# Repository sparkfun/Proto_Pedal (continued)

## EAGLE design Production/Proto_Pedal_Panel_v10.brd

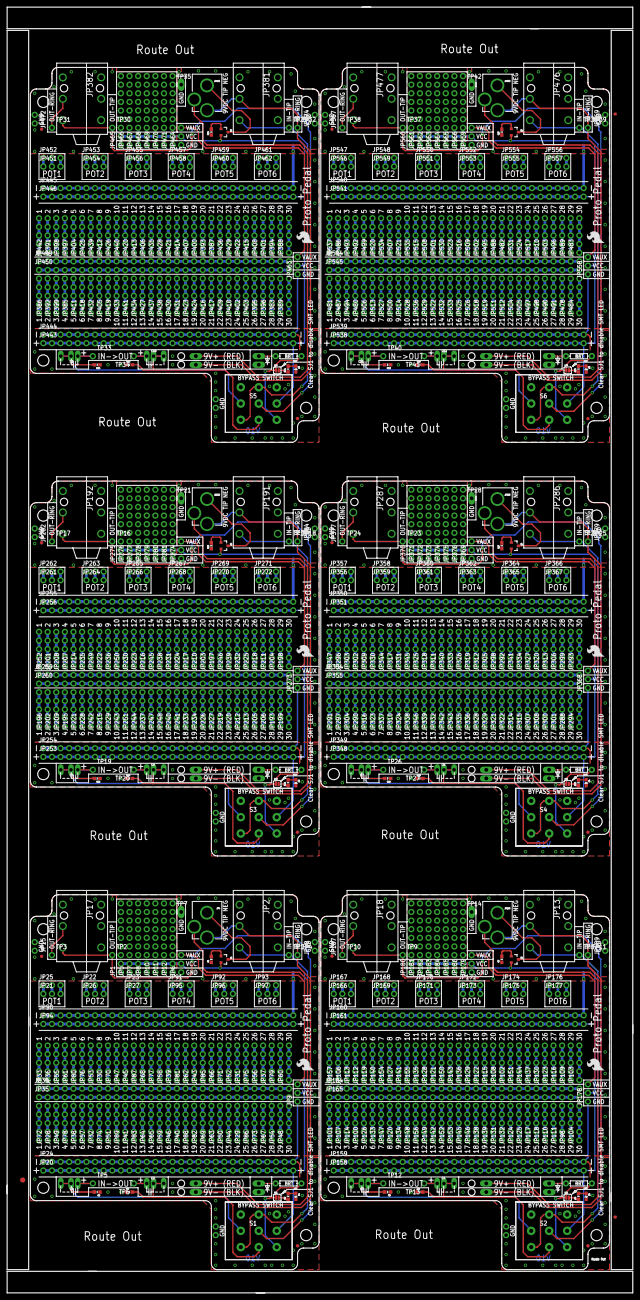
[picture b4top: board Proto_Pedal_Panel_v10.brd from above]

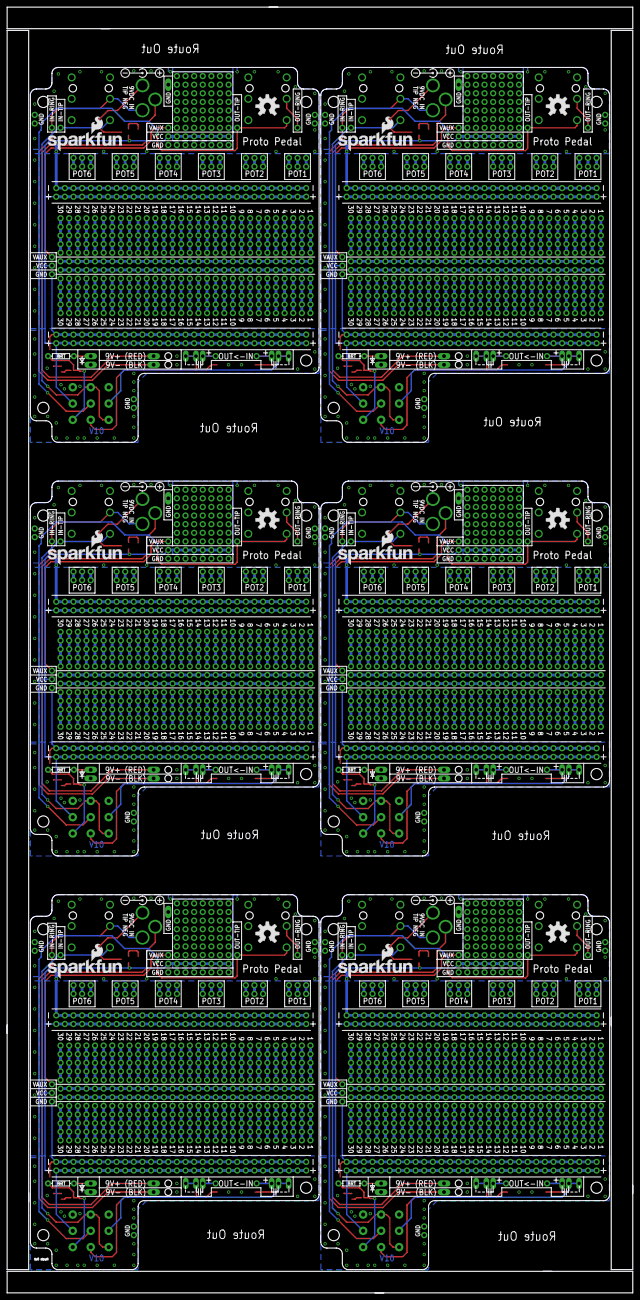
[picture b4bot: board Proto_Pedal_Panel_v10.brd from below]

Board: 2 copper layers, 184.4 x 379.0 mm, 735 parts (12 on the bottom side), 588 nets.

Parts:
C1, C3, C5, C7, C9, C11: C in; DUAL-CAP
C2, C4, C6, C8, C10, C12: C out; DUAL-CAP
D1, D2, D3, D4, D5, D6: RED; LED-0603
E$1: FIDUCIAL-1.5X3
E$5, E$6: FIDUCIAL-1X2
FID1, FID2, FID3, FID4, FID5, FID6, FID7, FID8, FID9, FID10, FID11, FID12: FIDUCIAL1X2; FIDUCIAL-1X2
JP1, JP5, JP7, JP8, JP10, JP11, JP12, JP180, JP181, JP182, JP183, JP184, JP185, JP186, JP275, JP276, JP277, JP278, JP279, JP280, JP281, JP370, JP371, JP372, JP373, JP374, JP375, JP376, JP465, JP466, JP467, JP468, JP469, JP470, JP471, JP560, JP561, JP562, JP563, JP564, JP565, JP566: 1x9; 1X09_NO_SILK
JP2, JP13, JP191, JP286, JP381, JP476: INPUT JACK; AUDIO-JACK-.25-INCH-HORIZ-PTH
JP3, JP163, JP258, JP353, JP448, JP543: 9VBattery; 1X02_LONGPADS
JP4, JP190, JP285, JP380, JP475, JP570: POWER_JACK_TIP_NEGATIVE; POWER-BARRELJACK-PTH-LOCK-FIXED
JP6, JP9, JP21, JP22, JP23, JP25, JP26, JP27, JP91, JP92, JP93, JP95, JP96, JP97, JP166, JP167, JP168, JP169, JP170, JP171, JP172, JP173, JP174, JP175, JP176, JP177, JP178, JP179, JP261, JP262, JP263, JP264, JP265, JP266, JP267, JP268, JP269, JP270, JP271, JP272, JP273, JP274, JP356, JP357, JP358, JP359, JP360, JP361, JP362, JP363, JP364, JP365, JP366, JP367, JP368, JP369, JP451, JP452, JP453, JP454, JP455, JP456, JP457, JP458, JP459, JP460, JP461, JP462, JP463, JP464, JP546, JP547, JP548, JP549, JP550, JP551, JP552, JP553, JP554, JP555, JP556, JP557, JP558, JP559: 1x3; 1X03_NO_SILK
JP14, JP162, JP257, JP352, JP447, JP542: PTH-LED; 1X02_LONGPADS
JP15, JP16, JP19, JP187, JP188, JP189, JP282, JP283, JP284, JP377, JP378, JP379, JP472, JP473, JP474, JP567, JP568, JP569: 1x2; 1X02_NO_SILK
JP17, JP18, JP192, JP287, JP382, JP477: OUTPUT JACK; AUDIO-JACK-.25-INCH-HORIZ-PTH
JP20, JP24, JP34, JP35, JP90, JP94, JP158, JP159, JP160, JP161, JP164, JP165, JP253, JP254, JP255, JP256, JP259, JP260, JP348, JP349, JP350, JP351, JP354, JP355, JP443, JP444, JP445, JP446, JP449, JP450, JP538, JP539, JP540, JP541, JP544, JP545: 1x30; 1X30_NO_SILK
JP28, JP29, JP30, JP31, JP32, JP33, JP36, JP37, JP38, JP39, JP40, JP41, JP42, JP43, JP44, JP45, JP46, JP47, JP48, JP49, JP50, JP51, JP52, JP53, JP54, JP55, JP56, JP57, JP58, JP59, JP60, JP61, JP62, JP63, JP64, JP65, JP66, JP67, JP68, JP69, JP70, JP71, JP72, JP73, JP74, JP75, JP76, JP77, JP78, JP79, JP80, JP81, JP82, JP83, JP84, JP85, JP86, JP87, JP88, JP98, JP99, JP100, JP101, JP102, JP103, JP104, JP105, JP106, JP107, JP108, JP109, JP110, JP111, JP112, JP113, JP114, JP115, JP116, JP117, JP118, JP119, JP120, JP121, JP122, JP123, JP124, JP125, JP126, JP127, JP128, JP129, JP130, JP131, JP132, JP133, JP134, JP135, JP136, JP137, JP138, JP139, JP140, JP141, JP142, JP143, JP144, JP145, JP146, JP147, JP149, JP150, JP151, JP152, JP153, JP154, JP155, JP156, JP157, JP193, JP194, JP195, JP196, JP197, JP198, JP199, JP200, JP201, JP202, JP203, JP204, JP205, JP206, JP207, JP208, JP209, JP210, JP211, JP212, JP213, JP214, JP215, JP216, JP217, JP218, JP219, JP220, JP221, JP222, JP223, JP224, JP225, JP226, JP227, JP228, JP229, JP230, JP231, JP232, JP233, JP234, JP235, JP236, JP237, JP238, JP239, JP240, JP241, JP242, JP244, JP245, JP246, JP247, JP248, JP249, JP250, JP251, JP252, JP288, JP289, JP290, JP291, JP292, JP293, JP294, JP295, JP296, JP297, JP298, JP299, JP300, JP301, JP302, JP303, JP304, JP305, JP306, JP307, JP308, JP309, JP310, JP311, JP312, JP313, JP314, JP315, JP316, JP317, JP318, JP319, JP320, JP321, JP322, JP323, JP324, JP325, JP326, JP327, JP328, JP329, JP330, JP331, JP332, JP333, JP334, JP335, JP336, JP337, JP339, JP340, JP341, JP342, JP343, JP344, JP345, JP346, JP347, JP383, JP384, JP385, JP386, JP387, JP388, JP389, JP390, JP391, JP392, JP393, JP394, JP395, JP396, JP397, JP398, JP399, JP400, JP401, JP402, JP403, JP404, JP405, JP406, JP407, JP408, JP409, JP410, JP411, JP412, JP413, JP414, JP415, JP416, JP417, JP418, JP419, JP420, JP421, JP422, JP423, JP424, JP425, JP426, JP427, JP428, JP429, JP430, JP431, JP432, JP434, JP435, JP436, JP437, JP438, JP439, JP440, JP441, JP442, JP478, JP479, JP480, JP481, JP482, JP483, JP484, JP485, JP486, JP487, JP488, JP489, JP490, JP491, JP492, JP493, JP494, JP495, JP496, JP497, JP498, JP499, JP500, JP501, JP502, JP503, JP504, JP505, JP506, JP507, JP508, JP509, JP510, JP511, JP512, JP513, JP514, JP515, JP516, JP517, JP518, JP519, JP520, JP521, JP522, JP523, JP524, JP525, JP526, JP527, JP529, JP530, JP531, JP532, JP533, JP534, JP535, JP536, JP537: 1x5; 1X05_NO_SILK
JP89, JP148, JP243, JP338, JP433, JP528: v; 1X05_NO_SILK
LOGO1, LOGO4, LOGO7, LOGO10, LOGO13, LOGO16: SFE_LOGO_NAME_FLAME.2_INCH; SFE_LOGO_NAME_FLAME_.2
LOGO2, LOGO5, LOGO8, LOGO11, LOGO14, LOGO17: OSHW-LOGOL; OSHW-LOGO-L
LOGO3, LOGO6, LOGO9, LOGO12, LOGO15, LOGO18: SFE_LOGO_FLAME.2_INCH; SFE_LOGO_FLAME_.2
Q1, Q2, Q3, Q4, Q5, Q6: 2.5A/30V; SOT23-3
R1, R2, R3, R7, R8, R9, R12, R13, R14, R17, R18, R19, R22, R23, R24, R27, R28, R29: 1M; 0603-RES
R4, R10, R15, R20, R25, R30: BRT; AXIAL-0.3
R5, R6, R11, R16, R21, R26: 1K; 0603-RES
S1, S2, S3, S4, S5, S6: SWITCH-3PDT; STOMP-SWITCH-3PDT
SJ1, SJ2, SJ3, SJ4, SJ5, SJ6: disable LED; PAD-JUMPER-2-NC_BY_PASTE_YES_SILK_FULL_BOX
STANDOFF1, STANDOFF2, STANDOFF3, STANDOFF4, STANDOFF5, STANDOFF6, STANDOFF7, STANDOFF8, STANDOFF9, STANDOFF10, STANDOFF11, STANDOFF12, STANDOFF13, STANDOFF14, STANDOFF15, STANDOFF16, STANDOFF17, STANDOFF18, STANDOFF19, STANDOFF20, STANDOFF21, STANDOFF22, STANDOFF23, STANDOFF24: STAND-OFF
TP1, TP8, TP15, TP22, TP29, TP36: Raw In; 1X01_NO_SILK
TP2, TP9, TP16, TP23, TP30, TP37: Raw Out; 1X01_NO_SILK
TP3, TP10, TP17, TP24, TP31, TP38: Out Ring; 1X01_NO_SILK
TP4, TP11, TP18, TP25, TP32, TP39: In Ring; 1X01_NO_SILK
TP5, TP12, TP19, TP26, TP33, TP40: FX Input; 1X01_NO_SILK
TP6, TP13, TP20, TP27, TP34, TP41: FX Output; 1X01_NO_SILK
TP7, TP14, TP21, TP28, TP35, TP42: Out Ring; 1X01_LONGPAD

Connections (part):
FX_IN: C1.P$2, C1.P$3, R2.2, S1.P$2
FX_IN1: C3.P$2, C3.P$3, R9.2, S2.P$2
FX_IN2: C5.P$2, C5.P$3, R14.2, S3.P$2
FX_IN3: C7.P$2, C7.P$3, R19.2, S4.P$2
FX_IN4: C9.P$2, C9.P$3, R24.2, S5.P$2
FX_IN5: C11.P$2, C11.P$3, R29.2, S6.P$2
FX_OUT: C2.P$2, C2.P$3, R3.2, S1.P$6
FX_OUT1: C4.P$2, C4.P$3, R8.2, S2.P$6
FX_OUT2: C6.P$2, C6.P$3, R13.2, S3.P$6
FX_OUT3: C8.P$2, C8.P$3, R18.2, S4.P$6
FX_OUT4: C10.P$2, C10.P$3, R23.2, S5.P$6
FX_OUT5: C12.P$2, C12.P$3, R28.2, S6.P$6
GND: D1.C, JP1.1, JP2.SLEEVE, JP5.1, JP6.1, JP7.1, JP8.1, JP9.1, JP10.1, JP11.1, JP12.1, JP14.2, JP15.1, JP15.2, JP16.1, JP16.2, JP17.SLEEVE, JP19.1, JP19.2, JP24.1, JP24.2, JP24.3, JP24.4, JP24.5, JP24.6, JP24.7, JP24.8, JP24.9, JP24.10, JP24.11, JP24.12, JP24.13, JP24.14, JP24.15, JP24.16, JP24.17, JP24.18, JP24.19, JP24.20, JP24.21, JP24.22, JP24.23, JP24.24, JP24.25, JP24.26, JP24.27, JP24.28, JP24.29, JP24.30, JP90.1, JP90.2, JP90.3, JP90.4, JP90.5, JP90.6, JP90.7, JP90.8, JP90.9, JP90.10, JP90.11, JP90.12, JP90.13, JP90.14, JP90.15, JP90.16, JP90.17, JP90.18, JP90.19, JP90.20, JP90.21, JP90.22, JP90.23, JP90.24, JP90.25, JP90.26, JP90.27, JP90.28, JP90.29, JP90.30, R1.1, R2.1, R3.1, S1.P$1, TP7.1
GND1: D2.C, JP13.SLEEVE, JP18.SLEEVE, JP159.1, JP159.2, JP159.3, JP159.4, JP159.5, JP159.6, JP159.7, JP159.8, JP159.9, JP159.10, JP159.11, JP159.12, JP159.13, JP159.14, JP159.15, JP159.16, JP159.17, JP159.18, JP159.19, JP159.20, JP159.21, JP159.22, JP159.23, JP159.24, JP159.25, JP159.26, JP159.27, JP159.28, JP159.29, JP159.30, JP160.1, JP160.2, JP160.3, JP160.4, JP160.5, JP160.6, JP160.7, JP160.8, JP160.9, JP160.10, JP160.11, JP160.12, JP160.13, JP160.14, JP160.15, JP160.16, JP160.17, JP160.18, JP160.19, JP160.20, JP160.21, JP160.22, JP160.23, JP160.24, JP160.25, JP160.26, JP160.27, JP160.28, JP160.29, JP160.30, JP162.2, JP178.1, JP179.1, JP180.1, JP181.1, JP182.1, JP183.1, JP184.1, JP185.1, JP186.1, JP187.1, JP187.2, JP188.1, JP188.2, JP189.1, JP189.2, R7.1, R8.1, R9.1, S2.P$1, TP14.1
GND2: D3.C, JP191.SLEEVE, JP192.SLEEVE, JP254.1, JP254.2, JP254.3, JP254.4, JP254.5, JP254.6, JP254.7, JP254.8, JP254.9, JP254.10, JP254.11, JP254.12, JP254.13, JP254.14, JP254.15, JP254.16, JP254.17, JP254.18, JP254.19, JP254.20, JP254.21, JP254.22, JP254.23, JP254.24, JP254.25, JP254.26, JP254.27, JP254.28, JP254.29, JP254.30, JP255.1, JP255.2, JP255.3, JP255.4, JP255.5, JP255.6, JP255.7, JP255.8, JP255.9, JP255.10, JP255.11, JP255.12, JP255.13, JP255.14, JP255.15, JP255.16, JP255.17, JP255.18, JP255.19, JP255.20, JP255.21, JP255.22, JP255.23, JP255.24, JP255.25, JP255.26, JP255.27, JP255.28, JP255.29, JP255.30, JP257.2, JP273.1, JP274.1, JP275.1, JP276.1, JP277.1, JP278.1, JP279.1, JP280.1, JP281.1, JP282.1, JP282.2, JP283.1, JP283.2, JP284.1, JP284.2, R12.1, R13.1, R14.1, S3.P$1, TP21.1
GND3: D4.C, JP286.SLEEVE, JP287.SLEEVE, JP349.1, JP349.2, JP349.3, JP349.4, JP349.5, JP349.6, JP349.7, JP349.8, JP349.9, JP349.10, JP349.11, JP349.12, JP349.13, JP349.14, JP349.15, JP349.16, JP349.17, JP349.18, JP349.19, JP349.20, JP349.21, JP349.22, JP349.23, JP349.24, JP349.25, JP349.26, JP349.27, JP349.28, JP349.29, JP349.30, JP350.1, JP350.2, JP350.3, JP350.4, JP350.5, JP350.6, JP350.7, JP350.8, JP350.9, JP350.10, JP350.11, JP350.12, JP350.13, JP350.14, JP350.15, JP350.16, JP350.17, JP350.18, JP350.19, JP350.20, JP350.21, JP350.22, JP350.23, JP350.24, JP350.25, JP350.26, JP350.27, JP350.28, JP350.29, JP350.30, JP352.2, JP368.1, JP369.1, JP370.1, JP371.1, JP372.1, JP373.1, JP374.1, JP375.1, JP376.1, JP377.1, JP377.2, JP378.1, JP378.2, JP379.1, JP379.2, R17.1, R18.1, R19.1, S4.P$1, TP28.1
GND4: D5.C, JP381.SLEEVE, JP382.SLEEVE, JP444.1, JP444.2, JP444.3, JP444.4, JP444.5, JP444.6, JP444.7, JP444.8, JP444.9, JP444.10, JP444.11, JP444.12, JP444.13, JP444.14, JP444.15, JP444.16, JP444.17, JP444.18, JP444.19, JP444.20, JP444.21, JP444.22, JP444.23, JP444.24, JP444.25, JP444.26, JP444.27, JP444.28, JP444.29, JP444.30, JP445.1, JP445.2, JP445.3, JP445.4, JP445.5, JP445.6, JP445.7, JP445.8, JP445.9, JP445.10, JP445.11, JP445.12, JP445.13, JP445.14, JP445.15, JP445.16, JP445.17, JP445.18, JP445.19, JP445.20, JP445.21, JP445.22, JP445.23, JP445.24, JP445.25, JP445.26, JP445.27, JP445.28, JP445.29, JP445.30, JP447.2, JP463.1, JP464.1, JP465.1, JP466.1, JP467.1, JP468.1, JP469.1, JP470.1, JP471.1, JP472.1, JP472.2, JP473.1, JP473.2, JP474.1, JP474.2, R22.1, R23.1, R24.1, S5.P$1, TP35.1
GND5: D6.C, JP476.SLEEVE, JP477.SLEEVE, JP539.1, JP539.2, JP539.3, JP539.4, JP539.5, JP539.6, JP539.7, JP539.8, JP539.9, JP539.10, JP539.11, JP539.12, JP539.13, JP539.14, JP539.15, JP539.16, JP539.17, JP539.18, JP539.19, JP539.20, JP539.21, JP539.22, JP539.23, JP539.24, JP539.25, JP539.26, JP539.27, JP539.28, JP539.29, JP539.30, JP540.1, JP540.2, JP540.3, JP540.4, JP540.5, JP540.6, JP540.7, JP540.8, JP540.9, JP540.10, JP540.11, JP540.12, JP540.13, JP540.14, JP540.15, JP540.16, JP540.17, JP540.18, JP540.19, JP540.20, JP540.21, JP540.22, JP540.23, JP540.24, JP540.25, JP540.26, JP540.27, JP540.28, JP540.29, JP540.30, JP542.2, JP558.1, JP559.1, JP560.1, JP561.1, JP562.1, JP563.1, JP564.1, JP565.1, JP566.1, JP567.1, JP567.2, JP568.1, JP568.2, JP569.1, JP569.2, R27.1, R28.1, R29.1, S6.P$1, TP42.1
LEDA: JP14.1, R4.P$2
LEDA1: JP162.1, R10.P$2
LEDA2: JP257.1, R15.P$2
LEDA3: JP352.1, R20.P$2
LEDA4: JP447.1, R25.P$2
LEDA5: JP542.1, R30.P$2
unnamed: JP84.1, JP84.2, JP84.3, JP84.4, JP84.5
unnamed: JP85.1, JP85.2, JP85.3, JP85.4, JP85.5
unnamed: JP86.1, JP86.2, JP86.3, JP86.4, JP86.5
unnamed: JP87.1, JP87.2, JP87.3, JP87.4, JP87.5
unnamed: JP54.1, JP54.2, JP54.3, JP54.4, JP54.5
unnamed: JP88.1, JP88.2, JP88.3, JP88.4, JP88.5
unnamed: JP78.1, JP78.2, JP78.3, JP78.4, JP78.5
unnamed: JP72.1, JP72.2, JP72.3, JP72.4, JP72.5
unnamed: JP66.1, JP66.2, JP66.3, JP66.4, JP66.5
unnamed: JP60.1, JP60.2, JP60.3, JP60.4, JP60.5
unnamed: JP48.1, JP48.2, JP48.3, JP48.4, JP48.5
unnamed: JP42.1, JP42.2, JP42.3, JP42.4, JP42.5
unnamed: JP36.1, JP36.2, JP36.3, JP36.4, JP36.5
unnamed: JP28.1, JP28.2, JP28.3, JP28.4, JP28.5
unnamed: JP89.1, JP89.2, JP89.3, JP89.4, JP89.5
unnamed: JP79.1, JP79.2, JP79.3, JP79.4, JP79.5
unnamed: JP73.1, JP73.2, JP73.3, JP73.4, JP73.5
unnamed: JP67.1, JP67.2, JP67.3, JP67.4, JP67.5
unnamed: JP61.1, JP61.2, JP61.3, JP61.4, JP61.5
unnamed: JP55.1, JP55.2, JP55.3, JP55.4, JP55.5
unnamed: JP49.1, JP49.2, JP49.3, JP49.4, JP49.5
unnamed: JP43.1, JP43.2, JP43.3, JP43.4, JP43.5
unnamed: JP37.1, JP37.2, JP37.3, JP37.4, JP37.5
unnamed: JP29.1, JP29.2, JP29.3, JP29.4, JP29.5
unnamed: D1.A, R5.2
unnamed: JP80.1, JP80.2, JP80.3, JP80.4, JP80.5
unnamed: JP74.1, JP74.2, JP74.3, JP74.4, JP74.5
unnamed: JP68.1, JP68.2, JP68.3, JP68.4, JP68.5
unnamed: JP62.1, JP62.2, JP62.3, JP62.4, JP62.5
unnamed: JP56.1, JP56.2, JP56.3, JP56.4, JP56.5
unnamed: JP50.1, JP50.2, JP50.3, JP50.4, JP50.5
unnamed: JP44.1, JP44.2, JP44.3, JP44.4, JP44.5
unnamed: JP38.1, JP38.2, JP38.3, JP38.4, JP38.5
unnamed: JP30.1, JP30.2, JP30.3, JP30.4, JP30.5
unnamed: R4.P$1, S1.P$9, SJ1.1
unnamed: JP81.1, JP81.2, JP81.3, JP81.4, JP81.5
unnamed: JP75.1, JP75.2, JP75.3, JP75.4, JP75.5
unnamed: JP69.1, JP69.2, JP69.3, JP69.4, JP69.5
unnamed: JP63.1, JP63.2, JP63.3, JP63.4, JP63.5
unnamed: JP57.1, JP57.2, JP57.3, JP57.4, JP57.5
unnamed: JP51.1, JP51.2, JP51.3, JP51.4, JP51.5
unnamed: JP45.1, JP45.2, JP45.3, JP45.4, JP45.5
unnamed: JP39.1, JP39.2, JP39.3, JP39.4, JP39.5
unnamed: JP31.1, JP31.2, JP31.3, JP31.4, JP31.5
unnamed: JP3.1, JP4.SLEEVE-NORMAL
unnamed: JP82.1, JP82.2, JP82.3, JP82.4, JP82.5
unnamed: JP76.1, JP76.2, JP76.3, JP76.4, JP76.5
unnamed: JP70.1, JP70.2, JP70.3, JP70.4, JP70.5
unnamed: JP64.1, JP64.2, JP64.3, JP64.4, JP64.5
unnamed: JP58.1, JP58.2, JP58.3, JP58.4, JP58.5
unnamed: JP52.1, JP52.2, JP52.3, JP52.4, JP52.5
unnamed: JP46.1, JP46.2, JP46.3, JP46.4, JP46.5
unnamed: JP40.1, JP40.2, JP40.3, JP40.4, JP40.5
unnamed: JP32.1, JP32.2, JP32.3, JP32.4, JP32.5
unnamed: JP2.RING, JP3.2, JP4.TIP, TP4.1
unnamed: JP83.1, JP83.2, JP83.3, JP83.4, JP83.5
unnamed: JP77.1, JP77.2, JP77.3, JP77.4, JP77.5
unnamed: JP71.1, JP71.2, JP71.3, JP71.4, JP71.5
unnamed: JP65.1, JP65.2, JP65.3, JP65.4, JP65.5
unnamed: JP59.1, JP59.2, JP59.3, JP59.4, JP59.5
unnamed: JP53.1, JP53.2, JP53.3, JP53.4, JP53.5
unnamed: JP47.1, JP47.2, JP47.3, JP47.4, JP47.5
unnamed: JP41.1, JP41.2, JP41.3, JP41.4, JP41.5
unnamed: JP33.1, JP33.2, JP33.3, JP33.4, JP33.5
unnamed: R5.1, SJ1.2
unnamed: JP17.RING, TP3.1
unnamed: C1.P$1, TP5.1
unnamed: C2.P$1, TP6.1
unnamed: JP13.TIP, S2.P$3, S2.P$4, TP8.1
unnamed: JP2.TIP, S1.P$3, S1.P$4, TP1.1
unnamed: JP17.TIP, S1.P$5, TP2.1
unnamed: JP18.TIP, S2.P$5, TP9.1
unnamed: JP98.1, JP98.2, JP98.3, JP98.4, JP98.5
unnamed: JP100.1, JP100.2, JP100.3, JP100.4, JP100.5
unnamed: Q1.1, R1.2
unnamed: JP101.1, JP101.2, JP101.3, JP101.4, JP101.5
unnamed: JP21.1, JP25.1
unnamed: JP102.1, JP102.2, JP102.3, JP102.4, JP102.5
unnamed: JP21.2, JP25.2
unnamed: JP103.1, JP103.2, JP103.3, JP103.4, JP103.5
unnamed: JP21.3, JP25.3
unnamed: JP104.1, JP104.2, JP104.3, JP104.4, JP104.5
unnamed: JP22.1, JP26.1
unnamed: JP105.1, JP105.2, JP105.3, JP105.4, JP105.5
unnamed: JP22.2, JP26.2
unnamed: JP106.1, JP106.2, JP106.3, JP106.4, JP106.5
unnamed: JP22.3, JP26.3
unnamed: JP107.1, JP107.2, JP107.3, JP107.4, JP107.5
unnamed: JP34.1, JP34.2, JP34.3, JP34.4, JP34.5, JP34.6, JP34.7, JP34.8, JP34.9, JP34.10, JP34.11, JP34.12, JP34.13, JP34.14, JP34.15, JP34.16, JP34.17, JP34.18, JP34.19, JP34.20, JP34.21, JP34.22, JP34.23, JP34.24, JP34.25, JP34.26, JP34.27, JP34.28, JP34.29, JP34.30
unnamed: JP35.1, JP35.2, JP35.3, JP35.4, JP35.5, JP35.6, JP35.7, JP35.8, JP35.9, JP35.10, JP35.11, JP35.12, JP35.13, JP35.14, JP35.15, JP35.16, JP35.17, JP35.18, JP35.19, JP35.20, JP35.21, JP35.22, JP35.23, JP35.24, JP35.25, JP35.26, JP35.27, JP35.28, JP35.29, JP35.30
unnamed: JP23.1, JP27.1
unnamed: JP109.1, JP109.2, JP109.3, JP109.4, JP109.5
unnamed: JP23.2, JP27.2
unnamed: JP23.3, JP27.3
unnamed: JP91.1, JP95.1
unnamed: JP91.2, JP95.2
unnamed: JP91.3, JP95.3
unnamed: JP92.1, JP96.1
unnamed: JP92.2, JP96.2
unnamed: JP92.3, JP96.3
unnamed: JP93.1, JP97.1
unnamed: JP93.2, JP97.2
unnamed: JP93.3, JP97.3
unnamed: JP110.1, JP110.2, JP110.3, JP110.4, JP110.5
unnamed: JP111.1, JP111.2, JP111.3, JP111.4, JP111.5
unnamed: JP112.1, JP112.2, JP112.3, JP112.4, JP112.5
unnamed: JP113.1, JP113.2, JP113.3, JP113.4, JP113.5
unnamed: JP114.1, JP114.2, JP114.3, JP114.4, JP114.5
unnamed: JP115.1, JP115.2, JP115.3, JP115.4, JP115.5
unnamed: JP116.1, JP116.2, JP116.3, JP116.4, JP116.5
unnamed: JP117.1, JP117.2, JP117.3, JP117.4, JP117.5
unnamed: JP119.1, JP119.2, JP119.3, JP119.4, JP119.5
unnamed: JP120.1, JP120.2, JP120.3, JP120.4, JP120.5
unnamed: JP121.1, JP121.2, JP121.3, JP121.4, JP121.5
unnamed: JP122.1, JP122.2, JP122.3, JP122.4, JP122.5
unnamed: JP123.1, JP123.2, JP123.3, JP123.4, JP123.5
unnamed: JP124.1, JP124.2, JP124.3, JP124.4, JP124.5
unnamed: JP125.1, JP125.2, JP125.3, JP125.4, JP125.5
unnamed: JP126.1, JP126.2, JP126.3, JP126.4, JP126.5
unnamed: JP127.1, JP127.2, JP127.3, JP127.4, JP127.5
unnamed: JP129.1, JP129.2, JP129.3, JP129.4, JP129.5
unnamed: JP130.1, JP130.2, JP130.3, JP130.4, JP130.5
unnamed: JP131.1, JP131.2, JP131.3, JP131.4, JP131.5
unnamed: JP132.1, JP132.2, JP132.3, JP132.4, JP132.5
unnamed: JP133.1, JP133.2, JP133.3, JP133.4, JP133.5
unnamed: JP134.1, JP134.2, JP134.3, JP134.4, JP134.5
unnamed: JP135.1, JP135.2, JP135.3, JP135.4, JP135.5
unnamed: JP136.1, JP136.2, JP136.3, JP136.4, JP136.5
unnamed: JP137.1, JP137.2, JP137.3, JP137.4, JP137.5
unnamed: JP139.1, JP139.2, JP139.3, JP139.4, JP139.5
unnamed: JP140.1, JP140.2, JP140.3, JP140.4, JP140.5
unnamed: JP141.1, JP141.2, JP141.3, JP141.4, JP141.5
unnamed: JP142.1, JP142.2, JP142.3, JP142.4, JP142.5
unnamed: JP143.1, JP143.2, JP143.3, JP143.4, JP143.5
unnamed: JP144.1, JP144.2, JP144.3, JP144.4, JP144.5
unnamed: JP145.1, JP145.2, JP145.3, JP145.4, JP145.5
unnamed: JP146.1, JP146.2, JP146.3, JP146.4, JP146.5
unnamed: JP147.1, JP147.2, JP147.3, JP147.4, JP147.5
unnamed: JP149.1, JP149.2, JP149.3, JP149.4, JP149.5
unnamed: JP150.1, JP150.2, JP150.3, JP150.4, JP150.5
unnamed: JP151.1, JP151.2, JP151.3, JP151.4, JP151.5
unnamed: JP152.1, JP152.2, JP152.3, JP152.4, JP152.5
unnamed: JP153.1, JP153.2, JP153.3, JP153.4, JP153.5
unnamed: JP154.1, JP154.2, JP154.3, JP154.4, JP154.5
unnamed: JP155.1, JP155.2, JP155.3, JP155.4, JP155.5
unnamed: JP156.1, JP156.2, JP156.3, JP156.4, JP156.5
unnamed: JP157.1, JP157.2, JP157.3, JP157.4, JP157.5
unnamed: Q2.1, R7.2
unnamed: JP164.1, JP164.2, JP164.3, JP164.4, JP164.5, JP164.6, JP164.7, JP164.8, JP164.9, JP164.10, JP164.11, JP164.12, JP164.13, JP164.14, JP164.15, JP164.16, JP164.17, JP164.18, JP164.19, JP164.20, JP164.21, JP164.22, JP164.23, JP164.24, JP164.25, JP164.26, JP164.27, JP164.28, JP164.29, JP164.30
unnamed: JP165.1, JP165.2, JP165.3, JP165.4, JP165.5, JP165.6, JP165.7, JP165.8, JP165.9, JP165.10, JP165.11, JP165.12, JP165.13, JP165.14, JP165.15, JP165.16, JP165.17, JP165.18, JP165.19, JP165.20, JP165.21, JP165.22, JP165.23, JP165.24, JP165.25, JP165.26, JP165.27, JP165.28, JP165.29, JP165.30
unnamed: JP166.1, JP167.1
unnamed: JP166.2, JP167.2
unnamed: JP166.3, JP167.3
unnamed: JP168.1, JP169.1
unnamed: JP168.2, JP169.2
unnamed: JP168.3, JP169.3
unnamed: JP170.1, JP171.1
unnamed: JP170.2, JP171.2
unnamed: JP170.3, JP171.3
unnamed: JP172.1, JP173.1
unnamed: JP172.2, JP173.2
unnamed: JP172.3, JP173.3
unnamed: JP174.1, JP175.1
unnamed: JP174.2, JP175.2
unnamed: JP174.3, JP175.3
unnamed: JP176.1, JP177.1
unnamed: JP176.2, JP177.2
unnamed: JP176.3, JP177.3
unnamed: JP108.1, JP108.2, JP108.3, JP108.4, JP108.5
unnamed: JP148.1, JP148.2, JP148.3, JP148.4, JP148.5
unnamed: JP138.1, JP138.2, JP138.3, JP138.4, JP138.5
unnamed: JP128.1, JP128.2, JP128.3, JP128.4, JP128.5
unnamed: JP118.1, JP118.2, JP118.3, JP118.4, JP118.5
unnamed: JP99.1, JP99.2, JP99.3, JP99.4, JP99.5
unnamed: D2.A, R6.2
unnamed: R10.P$1, S2.P$9, SJ2.1
unnamed: JP163.1, JP190.SLEEVE-NORMAL
unnamed: JP13.RING, JP163.2, JP190.TIP, TP11.1
unnamed: R6.1, SJ2.2
unnamed: JP18.RING, TP10.1
unnamed: C3.P$1, TP12.1
unnamed: C4.P$1, TP13.1
unnamed: JP191.TIP, S3.P$3, S3.P$4, TP15.1
unnamed: JP192.TIP, S3.P$5, TP16.1
unnamed: JP193.1, JP193.2, JP193.3, JP193.4, JP193.5
unnamed: JP195.1, JP195.2, JP195.3, JP195.4, JP195.5
unnamed: JP196.1, JP196.2, JP196.3, JP196.4, JP196.5
unnamed: JP197.1, JP197.2, JP197.3, JP197.4, JP197.5
unnamed: JP198.1, JP198.2, JP198.3, JP198.4, JP198.5
unnamed: JP199.1, JP199.2, JP199.3, JP199.4, JP199.5
unnamed: JP200.1, JP200.2, JP200.3, JP200.4, JP200.5
unnamed: JP201.1, JP201.2, JP201.3, JP201.4, JP201.5
unnamed: JP202.1, JP202.2, JP202.3, JP202.4, JP202.5
unnamed: JP204.1, JP204.2, JP204.3, JP204.4, JP204.5
unnamed: JP205.1, JP205.2, JP205.3, JP205.4, JP205.5
unnamed: JP206.1, JP206.2, JP206.3, JP206.4, JP206.5
unnamed: JP207.1, JP207.2, JP207.3, JP207.4, JP207.5
unnamed: JP208.1, JP208.2, JP208.3, JP208.4, JP208.5
unnamed: JP209.1, JP209.2, JP209.3, JP209.4, JP209.5
unnamed: JP210.1, JP210.2, JP210.3, JP210.4, JP210.5
unnamed: JP211.1, JP211.2, JP211.3, JP211.4, JP211.5
unnamed: JP212.1, JP212.2, JP212.3, JP212.4, JP212.5
unnamed: JP214.1, JP214.2, JP214.3, JP214.4, JP214.5
unnamed: JP215.1, JP215.2, JP215.3, JP215.4, JP215.5
unnamed: JP216.1, JP216.2, JP216.3, JP216.4, JP216.5
unnamed: JP217.1, JP217.2, JP217.3, JP217.4, JP217.5
unnamed: JP218.1, JP218.2, JP218.3, JP218.4, JP218.5
unnamed: JP219.1, JP219.2, JP219.3, JP219.4, JP219.5
unnamed: JP220.1, JP220.2, JP220.3, JP220.4, JP220.5
unnamed: JP221.1, JP221.2, JP221.3, JP221.4, JP221.5
unnamed: JP222.1, JP222.2, JP222.3, JP222.4, JP222.5
unnamed: JP224.1, JP224.2, JP224.3, JP224.4, JP224.5
unnamed: JP225.1, JP225.2, JP225.3, JP225.4, JP225.5
unnamed: JP226.1, JP226.2, JP226.3, JP226.4, JP226.5
unnamed: JP227.1, JP227.2, JP227.3, JP227.4, JP227.5
unnamed: JP228.1, JP228.2, JP228.3, JP228.4, JP228.5
unnamed: JP229.1, JP229.2, JP229.3, JP229.4, JP229.5
unnamed: JP230.1, JP230.2, JP230.3, JP230.4, JP230.5
unnamed: JP231.1, JP231.2, JP231.3, JP231.4, JP231.5
unnamed: JP232.1, JP232.2, JP232.3, JP232.4, JP232.5
unnamed: JP234.1, JP234.2, JP234.3, JP234.4, JP234.5
unnamed: JP235.1, JP235.2, JP235.3, JP235.4, JP235.5
unnamed: JP236.1, JP236.2, JP236.3, JP236.4, JP236.5
unnamed: JP237.1, JP237.2, JP237.3, JP237.4, JP237.5
unnamed: JP238.1, JP238.2, JP238.3, JP238.4, JP238.5
unnamed: JP239.1, JP239.2, JP239.3, JP239.4, JP239.5
unnamed: JP240.1, JP240.2, JP240.3, JP240.4, JP240.5
unnamed: JP241.1, JP241.2, JP241.3, JP241.4, JP241.5
unnamed: JP242.1, JP242.2, JP242.3, JP242.4, JP242.5
unnamed: JP244.1, JP244.2, JP244.3, JP244.4, JP244.5
unnamed: JP245.1, JP245.2, JP245.3, JP245.4, JP245.5
unnamed: JP246.1, JP246.2, JP246.3, JP246.4, JP246.5
unnamed: JP247.1, JP247.2, JP247.3, JP247.4, JP247.5
unnamed: JP248.1, JP248.2, JP248.3, JP248.4, JP248.5
unnamed: JP249.1, JP249.2, JP249.3, JP249.4, JP249.5
unnamed: JP250.1, JP250.2, JP250.3, JP250.4, JP250.5
unnamed: JP251.1, JP251.2, JP251.3, JP251.4, JP251.5
unnamed: JP252.1, JP252.2, JP252.3, JP252.4, JP252.5
unnamed: Q3.1, R12.2
unnamed: JP259.1, JP259.2, JP259.3, JP259.4, JP259.5, JP259.6, JP259.7, JP259.8, JP259.9, JP259.10, JP259.11, JP259.12, JP259.13, JP259.14, JP259.15, JP259.16, JP259.17, JP259.18, JP259.19, JP259.20, JP259.21, JP259.22, JP259.23, JP259.24, JP259.25, JP259.26, JP259.27, JP259.28, JP259.29, JP259.30
unnamed: JP260.1, JP260.2, JP260.3, JP260.4, JP260.5, JP260.6, JP260.7, JP260.8, JP260.9, JP260.10, JP260.11, JP260.12, JP260.13, JP260.14, JP260.15, JP260.16, JP260.17, JP260.18, JP260.19, JP260.20, JP260.21, JP260.22, JP260.23, JP260.24, JP260.25, JP260.26, JP260.27, JP260.28, JP260.29, JP260.30
unnamed: JP261.1, JP262.1
unnamed: JP261.2, JP262.2
unnamed: JP261.3, JP262.3
unnamed: JP263.1, JP264.1
unnamed: JP263.2, JP264.2
unnamed: JP263.3, JP264.3
unnamed: JP265.1, JP266.1
unnamed: JP265.2, JP266.2
unnamed: JP265.3, JP266.3
unnamed: JP267.1, JP268.1
unnamed: JP267.2, JP268.2
unnamed: JP267.3, JP268.3
unnamed: JP269.1, JP270.1
unnamed: JP269.2, JP270.2
unnamed: JP269.3, JP270.3
unnamed: JP271.1, JP272.1
unnamed: JP271.2, JP272.2
unnamed: JP271.3, JP272.3
unnamed: JP203.1, JP203.2, JP203.3, JP203.4, JP203.5
unnamed: JP243.1, JP243.2, JP243.3, JP243.4, JP243.5
unnamed: JP233.1, JP233.2, JP233.3, JP233.4, JP233.5
unnamed: JP223.1, JP223.2, JP223.3, JP223.4, JP223.5
unnamed: JP213.1, JP213.2, JP213.3, JP213.4, JP213.5
unnamed: JP194.1, JP194.2, JP194.3, JP194.4, JP194.5
unnamed: D3.A, R11.2
unnamed: R15.P$1, S3.P$9, SJ3.1
unnamed: JP258.1, JP285.SLEEVE-NORMAL
unnamed: JP191.RING, JP258.2, JP285.TIP, TP18.1
unnamed: R11.1, SJ3.2
unnamed: JP192.RING, TP17.1
unnamed: C5.P$1, TP19.1
unnamed: C6.P$1, TP20.1
unnamed: JP286.TIP, S4.P$3, S4.P$4, TP22.1
unnamed: JP287.TIP, S4.P$5, TP23.1
unnamed: JP288.1, JP288.2, JP288.3, JP288.4, JP288.5
unnamed: JP290.1, JP290.2, JP290.3, JP290.4, JP290.5
unnamed: JP291.1, JP291.2, JP291.3, JP291.4, JP291.5
unnamed: JP292.1, JP292.2, JP292.3, JP292.4, JP292.5
unnamed: JP293.1, JP293.2, JP293.3, JP293.4, JP293.5
unnamed: JP294.1, JP294.2, JP294.3, JP294.4, JP294.5
unnamed: JP295.1, JP295.2, JP295.3, JP295.4, JP295.5
unnamed: JP296.1, JP296.2, JP296.3, JP296.4, JP296.5
unnamed: JP297.1, JP297.2, JP297.3, JP297.4, JP297.5
unnamed: JP299.1, JP299.2, JP299.3, JP299.4, JP299.5
unnamed: JP300.1, JP300.2, JP300.3, JP300.4, JP300.5
unnamed: JP301.1, JP301.2, JP301.3, JP301.4, JP301.5
unnamed: JP302.1, JP302.2, JP302.3, JP302.4, JP302.5
unnamed: JP303.1, JP303.2, JP303.3, JP303.4, JP303.5
unnamed: JP304.1, JP304.2, JP304.3, JP304.4, JP304.5
unnamed: JP305.1, JP305.2, JP305.3, JP305.4, JP305.5
unnamed: JP306.1, JP306.2, JP306.3, JP306.4, JP306.5
unnamed: JP307.1, JP307.2, JP307.3, JP307.4, JP307.5
unnamed: JP309.1, JP309.2, JP309.3, JP309.4, JP309.5
unnamed: JP310.1, JP310.2, JP310.3, JP310.4, JP310.5
unnamed: JP311.1, JP311.2, JP311.3, JP311.4, JP311.5
unnamed: JP312.1, JP312.2, JP312.3, JP312.4, JP312.5
unnamed: JP313.1, JP313.2, JP313.3, JP313.4, JP313.5
unnamed: JP314.1, JP314.2, JP314.3, JP314.4, JP314.5
unnamed: JP315.1, JP315.2, JP315.3, JP315.4, JP315.5
unnamed: JP316.1, JP316.2, JP316.3, JP316.4, JP316.5
unnamed: JP317.1, JP317.2, JP317.3, JP317.4, JP317.5
unnamed: JP319.1, JP319.2, JP319.3, JP319.4, JP319.5
unnamed: JP320.1, JP320.2, JP320.3, JP320.4, JP320.5
unnamed: JP321.1, JP321.2, JP321.3, JP321.4, JP321.5
unnamed: JP322.1, JP322.2, JP322.3, JP322.4, JP322.5
unnamed: JP323.1, JP323.2, JP323.3, JP323.4, JP323.5
unnamed: JP324.1, JP324.2, JP324.3, JP324.4, JP324.5
unnamed: JP325.1, JP325.2, JP325.3, JP325.4, JP325.5
unnamed: JP326.1, JP326.2, JP326.3, JP326.4, JP326.5
unnamed: JP327.1, JP327.2, JP327.3, JP327.4, JP327.5
unnamed: JP329.1, JP329.2, JP329.3, JP329.4, JP329.5
unnamed: JP330.1, JP330.2, JP330.3, JP330.4, JP330.5
unnamed: JP331.1, JP331.2, JP331.3, JP331.4, JP331.5
unnamed: JP332.1, JP332.2, JP332.3, JP332.4, JP332.5
unnamed: JP333.1, JP333.2, JP333.3, JP333.4, JP333.5
unnamed: JP334.1, JP334.2, JP334.3, JP334.4, JP334.5
unnamed: JP335.1, JP335.2, JP335.3, JP335.4, JP335.5
unnamed: JP336.1, JP336.2, JP336.3, JP336.4, JP336.5
unnamed: JP337.1, JP337.2, JP337.3, JP337.4, JP337.5
unnamed: JP339.1, JP339.2, JP339.3, JP339.4, JP339.5
unnamed: JP340.1, JP340.2, JP340.3, JP340.4, JP340.5
unnamed: JP341.1, JP341.2, JP341.3, JP341.4, JP341.5
unnamed: JP342.1, JP342.2, JP342.3, JP342.4, JP342.5
unnamed: JP343.1, JP343.2, JP343.3, JP343.4, JP343.5
unnamed: JP344.1, JP344.2, JP344.3, JP344.4, JP344.5
unnamed: JP345.1, JP345.2, JP345.3, JP345.4, JP345.5
unnamed: JP346.1, JP346.2, JP346.3, JP346.4, JP346.5
unnamed: JP347.1, JP347.2, JP347.3, JP347.4, JP347.5
unnamed: Q4.1, R17.2
unnamed: JP354.1, JP354.2, JP354.3, JP354.4, JP354.5, JP354.6, JP354.7, JP354.8, JP354.9, JP354.10, JP354.11, JP354.12, JP354.13, JP354.14, JP354.15, JP354.16, JP354.17, JP354.18, JP354.19, JP354.20, JP354.21, JP354.22, JP354.23, JP354.24, JP354.25, JP354.26, JP354.27, JP354.28, JP354.29, JP354.30
unnamed: JP355.1, JP355.2, JP355.3, JP355.4, JP355.5, JP355.6, JP355.7, JP355.8, JP355.9, JP355.10, JP355.11, JP355.12, JP355.13, JP355.14, JP355.15, JP355.16, JP355.17, JP355.18, JP355.19, JP355.20, JP355.21, JP355.22, JP355.23, JP355.24, JP355.25, JP355.26, JP355.27, JP355.28, JP355.29, JP355.30
unnamed: JP356.1, JP357.1
unnamed: JP356.2, JP357.2
unnamed: JP356.3, JP357.3
unnamed: JP358.1, JP359.1
unnamed: JP358.2, JP359.2
unnamed: JP358.3, JP359.3
unnamed: JP360.1, JP361.1
unnamed: JP360.2, JP361.2
unnamed: JP360.3, JP361.3
unnamed: JP362.1, JP363.1
unnamed: JP362.2, JP363.2
unnamed: JP362.3, JP363.3
unnamed: JP364.1, JP365.1
unnamed: JP364.2, JP365.2
unnamed: JP364.3, JP365.3
unnamed: JP366.1, JP367.1
unnamed: JP366.2, JP367.2
unnamed: JP366.3, JP367.3
unnamed: JP298.1, JP298.2, JP298.3, JP298.4, JP298.5
unnamed: JP338.1, JP338.2, JP338.3, JP338.4, JP338.5
unnamed: JP328.1, JP328.2, JP328.3, JP328.4, JP328.5
unnamed: JP318.1, JP318.2, JP318.3, JP318.4, JP318.5
unnamed: JP308.1, JP308.2, JP308.3, JP308.4, JP308.5
unnamed: JP289.1, JP289.2, JP289.3, JP289.4, JP289.5
unnamed: D4.A, R16.2
unnamed: R20.P$1, S4.P$9, SJ4.1
unnamed: JP353.1, JP380.SLEEVE-NORMAL
unnamed: JP286.RING, JP353.2, JP380.TIP, TP25.1
unnamed: R16.1, SJ4.2
unnamed: JP287.RING, TP24.1
unnamed: C7.P$1, TP26.1
unnamed: C8.P$1, TP27.1
unnamed: JP381.TIP, S5.P$3, S5.P$4, TP29.1
unnamed: JP382.TIP, S5.P$5, TP30.1
unnamed: JP383.1, JP383.2, JP383.3, JP383.4, JP383.5
unnamed: JP385.1, JP385.2, JP385.3, JP385.4, JP385.5
unnamed: JP386.1, JP386.2, JP386.3, JP386.4, JP386.5
unnamed: JP387.1, JP387.2, JP387.3, JP387.4, JP387.5
unnamed: JP388.1, JP388.2, JP388.3, JP388.4, JP388.5
unnamed: JP389.1, JP389.2, JP389.3, JP389.4, JP389.5
unnamed: JP390.1, JP390.2, JP390.3, JP390.4, JP390.5
unnamed: JP391.1, JP391.2, JP391.3, JP391.4, JP391.5
unnamed: JP392.1, JP392.2, JP392.3, JP392.4, JP392.5
unnamed: JP394.1, JP394.2, JP394.3, JP394.4, JP394.5
unnamed: JP395.1, JP395.2, JP395.3, JP395.4, JP395.5
unnamed: JP396.1, JP396.2, JP396.3, JP396.4, JP396.5
unnamed: JP397.1, JP397.2, JP397.3, JP397.4, JP397.5
unnamed: JP398.1, JP398.2, JP398.3, JP398.4, JP398.5
unnamed: JP399.1, JP399.2, JP399.3, JP399.4, JP399.5
unnamed: JP400.1, JP400.2, JP400.3, JP400.4, JP400.5
unnamed: JP401.1, JP401.2, JP401.3, JP401.4, JP401.5
unnamed: JP402.1, JP402.2, JP402.3, JP402.4, JP402.5
unnamed: JP404.1, JP404.2, JP404.3, JP404.4, JP404.5
unnamed: JP405.1, JP405.2, JP405.3, JP405.4, JP405.5
unnamed: JP406.1, JP406.2, JP406.3, JP406.4, JP406.5
unnamed: JP407.1, JP407.2, JP407.3, JP407.4, JP407.5
unnamed: JP408.1, JP408.2, JP408.3, JP408.4, JP408.5
unnamed: JP409.1, JP409.2, JP409.3, JP409.4, JP409.5
unnamed: JP410.1, JP410.2, JP410.3, JP410.4, JP410.5
unnamed: JP411.1, JP411.2, JP411.3, JP411.4, JP411.5
unnamed: JP412.1, JP412.2, JP412.3, JP412.4, JP412.5
unnamed: JP414.1, JP414.2, JP414.3, JP414.4, JP414.5
unnamed: JP415.1, JP415.2, JP415.3, JP415.4, JP415.5
unnamed: JP416.1, JP416.2, JP416.3, JP416.4, JP416.5
unnamed: JP417.1, JP417.2, JP417.3, JP417.4, JP417.5
unnamed: JP418.1, JP418.2, JP418.3, JP418.4, JP418.5
unnamed: JP419.1, JP419.2, JP419.3, JP419.4, JP419.5
unnamed: JP420.1, JP420.2, JP420.3, JP420.4, JP420.5
unnamed: JP421.1, JP421.2, JP421.3, JP421.4, JP421.5
unnamed: JP422.1, JP422.2, JP422.3, JP422.4, JP422.5
unnamed: JP424.1, JP424.2, JP424.3, JP424.4, JP424.5
unnamed: JP425.1, JP425.2, JP425.3, JP425.4, JP425.5
unnamed: JP426.1, JP426.2, JP426.3, JP426.4, JP426.5
unnamed: JP427.1, JP427.2, JP427.3, JP427.4, JP427.5
unnamed: JP428.1, JP428.2, JP428.3, JP428.4, JP428.5
unnamed: JP429.1, JP429.2, JP429.3, JP429.4, JP429.5
unnamed: JP430.1, JP430.2, JP430.3, JP430.4, JP430.5
unnamed: JP431.1, JP431.2, JP431.3, JP431.4, JP431.5
unnamed: JP432.1, JP432.2, JP432.3, JP432.4, JP432.5
unnamed: JP434.1, JP434.2, JP434.3, JP434.4, JP434.5
unnamed: JP435.1, JP435.2, JP435.3, JP435.4, JP435.5
unnamed: JP436.1, JP436.2, JP436.3, JP436.4, JP436.5
unnamed: JP437.1, JP437.2, JP437.3, JP437.4, JP437.5
unnamed: JP438.1, JP438.2, JP438.3, JP438.4, JP438.5
unnamed: JP439.1, JP439.2, JP439.3, JP439.4, JP439.5
unnamed: JP440.1, JP440.2, JP440.3, JP440.4, JP440.5
unnamed: JP441.1, JP441.2, JP441.3, JP441.4, JP441.5
unnamed: JP442.1, JP442.2, JP442.3, JP442.4, JP442.5
unnamed: Q5.1, R22.2
unnamed: JP449.1, JP449.2, JP449.3, JP449.4, JP449.5, JP449.6, JP449.7, JP449.8, JP449.9, JP449.10, JP449.11, JP449.12, JP449.13, JP449.14, JP449.15, JP449.16, JP449.17, JP449.18, JP449.19, JP449.20, JP449.21, JP449.22, JP449.23, JP449.24, JP449.25, JP449.26, JP449.27, JP449.28, JP449.29, JP449.30
unnamed: JP450.1, JP450.2, JP450.3, JP450.4, JP450.5, JP450.6, JP450.7, JP450.8, JP450.9, JP450.10, JP450.11, JP450.12, JP450.13, JP450.14, JP450.15, JP450.16, JP450.17, JP450.18, JP450.19, JP450.20, JP450.21, JP450.22, JP450.23, JP450.24, JP450.25, JP450.26, JP450.27, JP450.28, JP450.29, JP450.30
unnamed: JP451.1, JP452.1
unnamed: JP451.2, JP452.2
unnamed: JP451.3, JP452.3
unnamed: JP453.1, JP454.1
unnamed: JP453.2, JP454.2
unnamed: JP453.3, JP454.3
unnamed: JP455.1, JP456.1
unnamed: JP455.2, JP456.2
unnamed: JP455.3, JP456.3
unnamed: JP457.1, JP458.1
unnamed: JP457.2, JP458.2
unnamed: JP457.3, JP458.3
unnamed: JP459.1, JP460.1
unnamed: JP459.2, JP460.2
unnamed: JP459.3, JP460.3
unnamed: JP461.1, JP462.1
unnamed: JP461.2, JP462.2
unnamed: JP461.3, JP462.3
unnamed: JP393.1, JP393.2, JP393.3, JP393.4, JP393.5
unnamed: JP433.1, JP433.2, JP433.3, JP433.4, JP433.5
unnamed: JP423.1, JP423.2, JP423.3, JP423.4, JP423.5
unnamed: JP413.1, JP413.2, JP413.3, JP413.4, JP413.5
unnamed: JP403.1, JP403.2, JP403.3, JP403.4, JP403.5
unnamed: JP384.1, JP384.2, JP384.3, JP384.4, JP384.5
unnamed: D5.A, R21.2
unnamed: R25.P$1, S5.P$9, SJ5.1
unnamed: JP448.1, JP475.SLEEVE-NORMAL
unnamed: JP381.RING, JP448.2, JP475.TIP, TP32.1
unnamed: R21.1, SJ5.2
unnamed: JP382.RING, TP31.1
unnamed: C9.P$1, TP33.1
unnamed: C10.P$1, TP34.1
unnamed: JP476.TIP, S6.P$3, S6.P$4, TP36.1
unnamed: JP477.TIP, S6.P$5, TP37.1
unnamed: JP478.1, JP478.2, JP478.3, JP478.4, JP478.5
unnamed: JP480.1, JP480.2, JP480.3, JP480.4, JP480.5
unnamed: JP481.1, JP481.2, JP481.3, JP481.4, JP481.5
unnamed: JP482.1, JP482.2, JP482.3, JP482.4, JP482.5
unnamed: JP483.1, JP483.2, JP483.3, JP483.4, JP483.5
unnamed: JP484.1, JP484.2, JP484.3, JP484.4, JP484.5
unnamed: JP485.1, JP485.2, JP485.3, JP485.4, JP485.5
unnamed: JP486.1, JP486.2, JP486.3, JP486.4, JP486.5
unnamed: JP487.1, JP487.2, JP487.3, JP487.4, JP487.5
unnamed: JP489.1, JP489.2, JP489.3, JP489.4, JP489.5
unnamed: JP490.1, JP490.2, JP490.3, JP490.4, JP490.5
unnamed: JP491.1, JP491.2, JP491.3, JP491.4, JP491.5
unnamed: JP492.1, JP492.2, JP492.3, JP492.4, JP492.5
unnamed: JP493.1, JP493.2, JP493.3, JP493.4, JP493.5
unnamed: JP494.1, JP494.2, JP494.3, JP494.4, JP494.5
unnamed: JP495.1, JP495.2, JP495.3, JP495.4, JP495.5
unnamed: JP496.1, JP496.2, JP496.3, JP496.4, JP496.5
unnamed: JP497.1, JP497.2, JP497.3, JP497.4, JP497.5
unnamed: JP499.1, JP499.2, JP499.3, JP499.4, JP499.5
unnamed: JP500.1, JP500.2, JP500.3, JP500.4, JP500.5
unnamed: JP501.1, JP501.2, JP501.3, JP501.4, JP501.5
unnamed: JP502.1, JP502.2, JP502.3, JP502.4, JP502.5
unnamed: JP503.1, JP503.2, JP503.3, JP503.4, JP503.5
unnamed: JP504.1, JP504.2, JP504.3, JP504.4, JP504.5
unnamed: JP505.1, JP505.2, JP505.3, JP505.4, JP505.5
unnamed: JP506.1, JP506.2, JP506.3, JP506.4, JP506.5
unnamed: JP507.1, JP507.2, JP507.3, JP507.4, JP507.5
unnamed: JP509.1, JP509.2, JP509.3, JP509.4, JP509.5
unnamed: JP510.1, JP510.2, JP510.3, JP510.4, JP510.5
unnamed: JP511.1, JP511.2, JP511.3, JP511.4, JP511.5
unnamed: JP512.1, JP512.2, JP512.3, JP512.4, JP512.5
unnamed: JP513.1, JP513.2, JP513.3, JP513.4, JP513.5
unnamed: JP514.1, JP514.2, JP514.3, JP514.4, JP514.5
unnamed: JP515.1, JP515.2, JP515.3, JP515.4, JP515.5
unnamed: JP516.1, JP516.2, JP516.3, JP516.4, JP516.5
unnamed: JP517.1, JP517.2, JP517.3, JP517.4, JP517.5
unnamed: JP519.1, JP519.2, JP519.3, JP519.4, JP519.5
unnamed: JP520.1, JP520.2, JP520.3, JP520.4, JP520.5
unnamed: JP521.1, JP521.2, JP521.3, JP521.4, JP521.5
unnamed: JP522.1, JP522.2, JP522.3, JP522.4, JP522.5
unnamed: JP523.1, JP523.2, JP523.3, JP523.4, JP523.5
unnamed: JP524.1, JP524.2, JP524.3, JP524.4, JP524.5
unnamed: JP525.1, JP525.2, JP525.3, JP525.4, JP525.5
unnamed: JP526.1, JP526.2, JP526.3, JP526.4, JP526.5
unnamed: JP527.1, JP527.2, JP527.3, JP527.4, JP527.5
unnamed: JP529.1, JP529.2, JP529.3, JP529.4, JP529.5
unnamed: JP530.1, JP530.2, JP530.3, JP530.4, JP530.5
unnamed: JP531.1, JP531.2, JP531.3, JP531.4, JP531.5
unnamed: JP532.1, JP532.2, JP532.3, JP532.4, JP532.5
unnamed: JP533.1, JP533.2, JP533.3, JP533.4, JP533.5
unnamed: JP534.1, JP534.2, JP534.3, JP534.4, JP534.5
unnamed: JP535.1, JP535.2, JP535.3, JP535.4, JP535.5
unnamed: JP536.1, JP536.2, JP536.3, JP536.4, JP536.5
unnamed: JP537.1, JP537.2, JP537.3, JP537.4, JP537.5
unnamed: Q6.1, R27.2
unnamed: JP544.1, JP544.2, JP544.3, JP544.4, JP544.5, JP544.6, JP544.7, JP544.8, JP544.9, JP544.10, JP544.11, JP544.12, JP544.13, JP544.14, JP544.15, JP544.16, JP544.17, JP544.18, JP544.19, JP544.20, JP544.21, JP544.22, JP544.23, JP544.24, JP544.25, JP544.26, JP544.27, JP544.28, JP544.29, JP544.30
unnamed: JP545.1, JP545.2, JP545.3, JP545.4, JP545.5, JP545.6, JP545.7, JP545.8, JP545.9, JP545.10, JP545.11, JP545.12, JP545.13, JP545.14, JP545.15, JP545.16, JP545.17, JP545.18, JP545.19, JP545.20, JP545.21, JP545.22, JP545.23, JP545.24, JP545.25, JP545.26, JP545.27, JP545.28, JP545.29, JP545.30
unnamed: JP546.1, JP547.1
unnamed: JP546.2, JP547.2
unnamed: JP546.3, JP547.3
unnamed: JP548.1, JP549.1
unnamed: JP548.2, JP549.2
unnamed: JP548.3, JP549.3
unnamed: JP550.1, JP551.1
unnamed: JP550.2, JP551.2
unnamed: JP550.3, JP551.3
unnamed: JP552.1, JP553.1
unnamed: JP552.2, JP553.2
unnamed: JP552.3, JP553.3
unnamed: JP554.1, JP555.1
unnamed: JP554.2, JP555.2
unnamed: JP554.3, JP555.3
unnamed: JP556.1, JP557.1
unnamed: JP556.2, JP557.2
unnamed: JP556.3, JP557.3
unnamed: JP488.1, JP488.2, JP488.3, JP488.4, JP488.5
unnamed: JP528.1, JP528.2, JP528.3, JP528.4, JP528.5
unnamed: JP518.1, JP518.2, JP518.3, JP518.4, JP518.5
unnamed: JP508.1, JP508.2, JP508.3, JP508.4, JP508.5
unnamed: JP498.1, JP498.2, JP498.3, JP498.4, JP498.5
unnamed: JP479.1, JP479.2, JP479.3, JP479.4, JP479.5
unnamed: D6.A, R26.2
unnamed: R30.P$1, S6.P$9, SJ6.1
unnamed: JP543.1, JP570.SLEEVE-NORMAL
unnamed: JP476.RING, JP543.2, JP570.TIP, TP39.1
unnamed: R26.1, SJ6.2
unnamed: JP477.RING, TP38.1
unnamed: C11.P$1, TP40.1
unnamed: C12.P$1, TP41.1
VAUX: JP6.3, JP9.3
VAUX1: JP178.3, JP179.3
VAUX2: JP273.3, JP274.3
VAUX3: JP368.3, JP369.3
VAUX4: JP463.3, JP464.3
VAUX5: JP558.3, JP559.3
VBATT: JP4.SLEEVE, Q1.3
VBATT1: JP190.SLEEVE, Q2.3
VBATT2: JP285.SLEEVE, Q3.3
VBATT3: JP380.SLEEVE, Q4.3
VBATT4: JP475.SLEEVE, Q5.3
VBATT5: JP570.SLEEVE, Q6.3
VCC: JP1.2, JP5.2, JP6.2, JP7.2, JP8.2, JP9.2, JP10.2, JP11.2, JP12.2, JP20.1, JP20.2, JP20.3, JP20.4, JP20.5, JP20.6, JP20.7, JP20.8, JP20.9, JP20.10, JP20.11, JP20.12, JP20.13, JP20.14, JP20.15, JP20.16, JP20.17, JP20.18, JP20.19, JP20.20, JP20.21, JP20.22, JP20.23, JP20.24, JP20.25, JP20.26, JP20.27, JP20.28, JP20.29, JP20.30, JP94.1, JP94.2, JP94.3, JP94.4, JP94.5, JP94.6, JP94.7, JP94.8, JP94.9, JP94.10, JP94.11, JP94.12, JP94.13, JP94.14, JP94.15, JP94.16, JP94.17, JP94.18, JP94.19, JP94.20, JP94.21, JP94.22, JP94.23, JP94.24, JP94.25, JP94.26, JP94.27, JP94.28, JP94.29, JP94.30, Q1.2, S1.P$8
VCC1: JP158.1, JP158.2, JP158.3, JP158.4, JP158.5, JP158.6, JP158.7, JP158.8, JP158.9, JP158.10, JP158.11, JP158.12, JP158.13, JP158.14, JP158.15, JP158.16, JP158.17, JP158.18, JP158.19, JP158.20, JP158.21, JP158.22, JP158.23, JP158.24, JP158.25, JP158.26, JP158.27, JP158.28, JP158.29, JP158.30, JP161.1, JP161.2, JP161.3, JP161.4, JP161.5, JP161.6, JP161.7, JP161.8, JP161.9, JP161.10, JP161.11, JP161.12, JP161.13, JP161.14, JP161.15, JP161.16, JP161.17, JP161.18, JP161.19, JP161.20, JP161.21, JP161.22, JP161.23, JP161.24, JP161.25, JP161.26, JP161.27, JP161.28, JP161.29, JP161.30, JP178.2, JP179.2, JP180.2, JP181.2, JP182.2, JP183.2, JP184.2, JP185.2, JP186.2, Q2.2, S2.P$8
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
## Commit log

2014-09-18 Initial Commit
    Boilderplate and WIP PCB files
2014-09-22 PCB Ready for protos
2015-10-12 WIP.
    Redid bypass switch to 3PDT component with multiple gates.
    Removed questionable LED circuit, replaced with an actual switch
    section.
2015-11-03 More WIP
    Many more changes based on prototype review.
    -Tip-negative power input.
    -uncommited proto space for power regulation.
    -Rail splitter removed
    -Strain relief near 9V snap
    -Some test points on i/O jacks
2015-11-04 More WIP.
    -Columns labeled.
    -Traces complete.
    -Text & silk more complete & organized.
2015-11-05 More WIP
    Much cleanup for review soon.
2015-11-06 Preparing for review
    Lots of little touch ups.
2015-11-10 Updates after group review.
    PTH power connector.
    PTH LED bias resistor.
2015-11-13 Relaxed design to use standard DRU
    Fixed funny pour shapes
    Relocated a couple traces
    Renumbered parts
2015-11-19 A couple of fixes after review.
    Fixed spelling of sililar.
    One piece of top silk had fallen to bottom - now corrected.
2016-02-16 Adding updated files from bench testing.
2016-03-11 added model of hammond style enclosure with cutouts for jacks and LED
2016-03-21 Updates based on proto evaluation.
    Usability & fit'n'finish issues solved.
2016-03-22 PCB updates after Marshall looked closer.
    A new more nits cleaned up.
2016-03-22 Adding SPICE sim of a pedal design
    Also adding spice intermediate files to .gitignore.
2016-03-22 Tweaks from checklist.
    - and + signs on rails are a bit smaller.
    +'s next to C1 and C2 were overlapping bare copper.
    Version bumped to V03.
2016-03-25 Moved ground hole to center, made r=1.65mm, d=3.3 for 1/8 inch bit to cut.
2016-04-12 added drawing exports
2016-05-02 Adding solidworks drawing & preview render.
2016-06-14 Silkscreen touchups from V03 proto.
    Prepping for redboard review.
    Rolling version to V10.
2016-06-20 Updates to board following group review.
    Added bottom-layer traces on I/O caps.
    Updated dimensions for standoff holes.
2016-06-20 Checklist review changes
    Bumping silk outlines for connectors to .008" (up from .005)
2016-06-20 Fixing what Eric found in review.
    -I/O coupling caps now have similar trace arrangements.
    -Second page of Schem bumped to V10.
2016-06-23 created panel v10
2016-09-21 Adding Throughput sketch for Teensy
    Should pass audio input to output, and print serial disgnostics of the 5
    ADC inputs.
2016-09-21 Added insulator card drawing and pdf
2016-09-21 Added parameter control and readme.md
2016-09-21 added description to readme
2016-09-22 Adding echo sketch.
    Still a bit messy, but need to check it in.
2016-09-22 Waypoint on delay sketch.
    working, but not super amazing jusrt yet.
2016-09-22 Perhaps some slight improvements.
    Making controls a little more stable.
2016-09-23 More incremental work on the echo.
2016-09-23 Adding readme for echo.
2016-09-23 Optimizing out the second mixer.
2016-09-23 Adding solidworks part for enclosure
2016-09-23 Adding files for gyrator EQ
2016-09-23 Adding files for Teensy projects
2016-09-23 Updating .gitignore to skip eagle library backups.
2016-09-23 Finalizing license and readme files.
